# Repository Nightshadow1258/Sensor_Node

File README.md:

# Sensor Node Version 3.50
This is an intermediate version before I decided to move to a two part design.
I split the MCU Board into its own small form factor PCB with connectors on the bottom side to connect to a base board. The inspiration comes from the raspberry compute module. This will allow me to reuse the MCU for different design in the future.

## Components
- NRF52840 (MCU)
- NPM1300 (PMIC)
- BQ29700 (Battery Protection IC)
- SHT40 (Temp & Humidity Sensor)
- USB (charging & data transfer)

# Archive Notice

This repository has been archived and is no longer maintained.
It contains historical versions of the Sensor Node project (V1.00, V2.00, etc.)
for reference and backup purposes.

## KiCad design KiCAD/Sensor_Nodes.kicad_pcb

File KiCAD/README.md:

# Sensor Node V3.00 Hardware
This folder contains the KiCAD files for the Sensor Node Version 3.00.

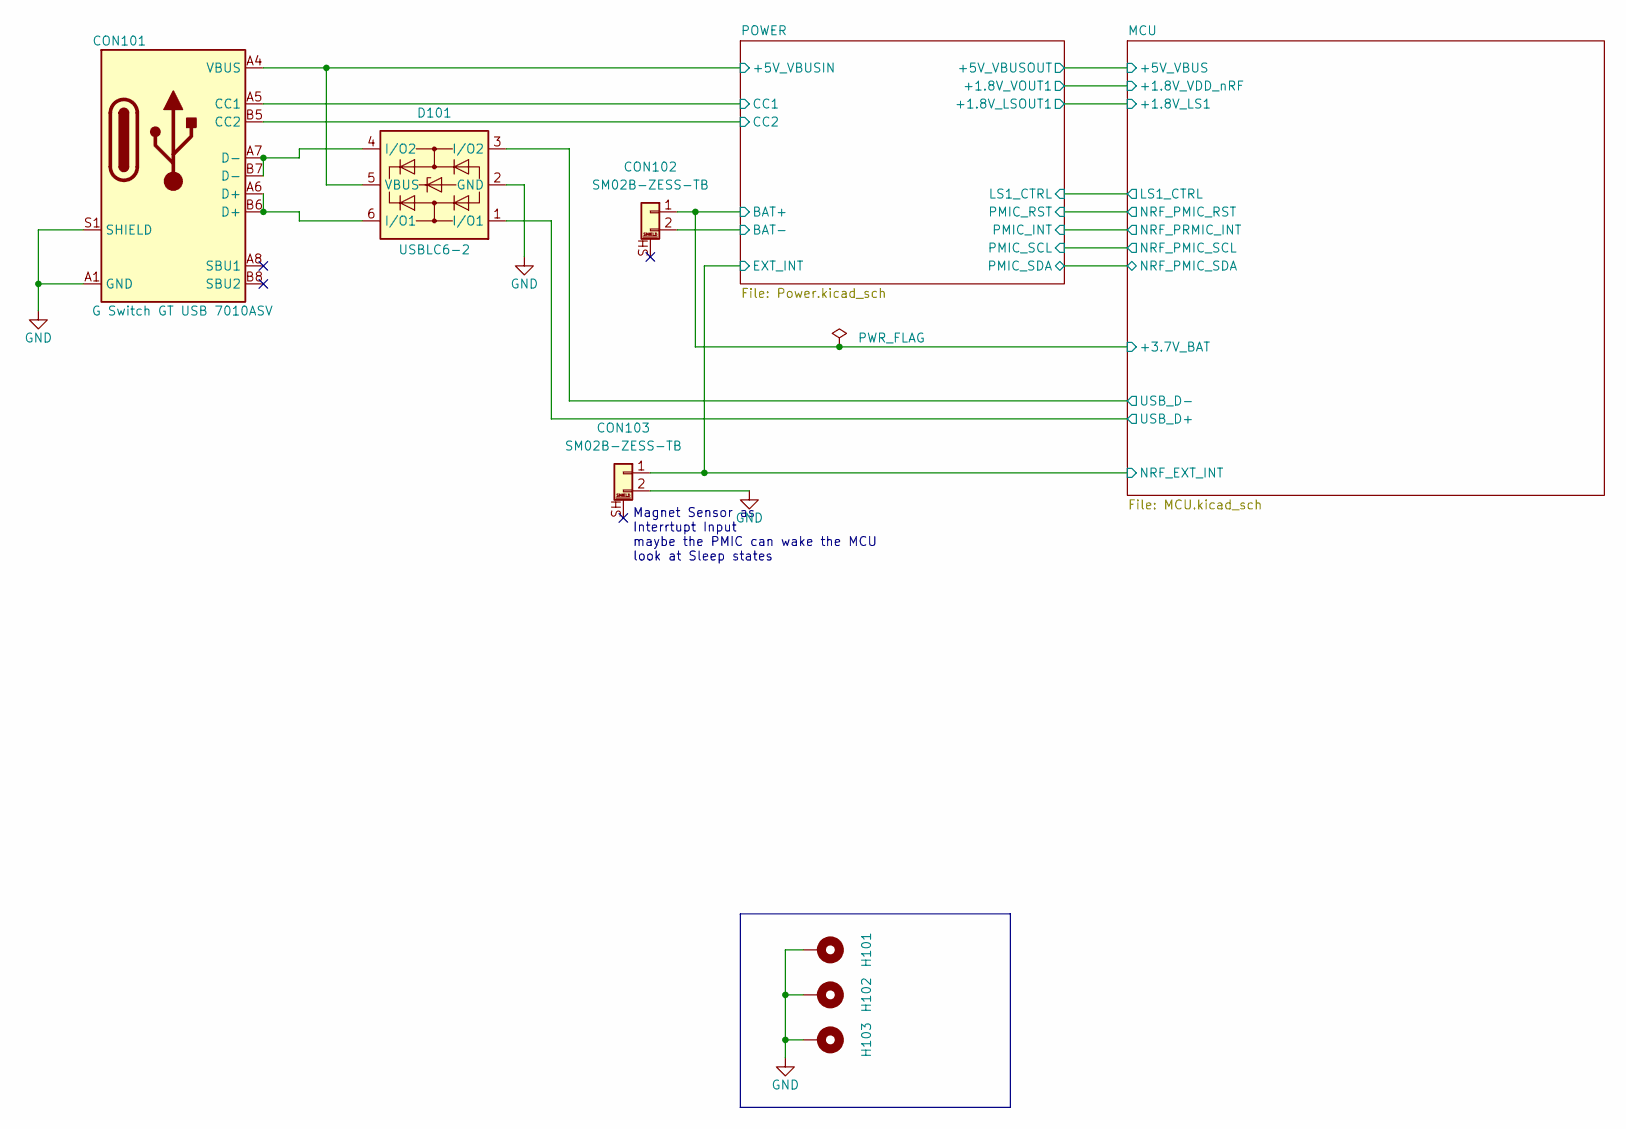
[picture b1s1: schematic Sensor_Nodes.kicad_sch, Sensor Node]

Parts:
CON101: G Switch GT USB 7010ASV; CON-GEN-USB_C-16P; LCSC Part # C2988369
CON102, CON103: SM02B-ZESS-TB; CON-SM02B-ZESS_TB
D101: USBLC6-2; SOT-23-6; LCSC Part # C7519
H101, H102, H103: MountingHole_Pad; MountingHole_3.2mm_M3_Pad_Via

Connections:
/MCU/NRF_EXT_INT: CON103.1; also elsewhere on the board
/MCU/USB_D+: D101.1 (I/O1); also elsewhere on the board
/MCU/USB_D-: D101.3 (I/O2); also elsewhere on the board
/POWER/+5V_VBUSIN: CON101.A4 (VBUS), CON101.A9 (VBUS), CON101.B4 (VBUS), CON101.B9 (VBUS), D101.5 (VBUS); also elsewhere on the board
/POWER/CC1: CON101.A5 (CC1); also elsewhere on the board
/POWER/CC2: CON101.B5 (CC2); also elsewhere on the board
GND: CON101.A1 (GND), CON101.A12 (GND), CON101.B1 (GND), CON101.B12 (GND), CON101.S1 (SHIELD), CON103.2, D101.2 (GND), H101.1, H102.1, H103.1; also elsewhere on the board
unnamed: CON101.A6 (D+), CON101.B6 (D+), D101.6 (I/O1)
unnamed: CON101.A7 (D-), CON101.B7 (D-), D101.4 (I/O2)

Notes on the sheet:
Magnet Sensor as Interrtupt Input maybe the PMIC can wake the MCU look at Sleep states

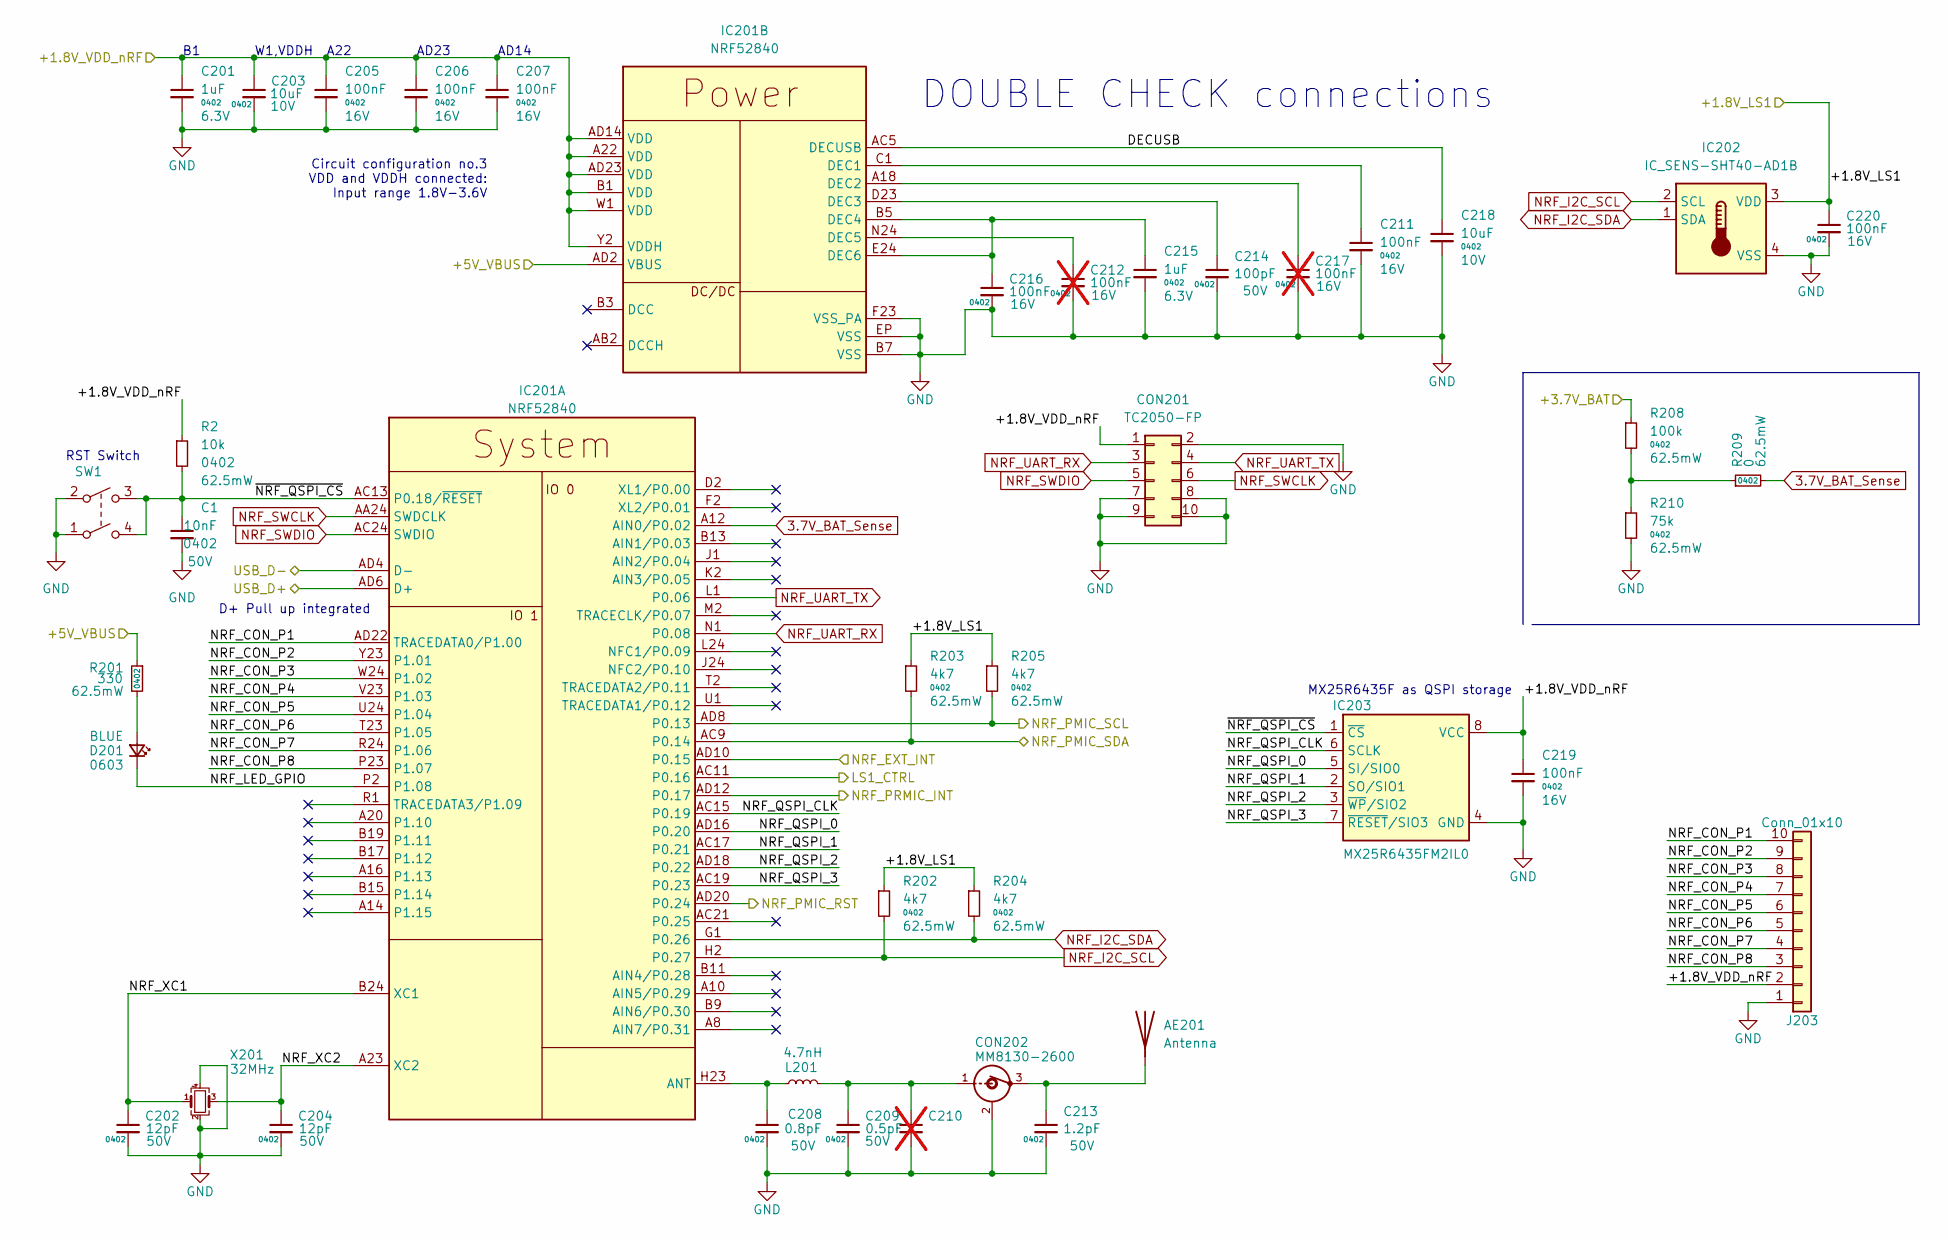
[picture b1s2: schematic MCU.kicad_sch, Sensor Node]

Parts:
AE201: Antenna; RF_ANT_NRF52840
C1: 10nF; C_0402_1005Metric; Voltage 50V; LCSC Part # C15195
C201, C215: 1uF; C_0402_1005Metric; Voltage 6.3V; LCSC Part # C15525
C202, C204: 12pF; C_0402_1005Metric; Voltage 50V; LCSC Part # C1547
C203, C218: 10uF; C_0603_1608Metric; Voltage 10V; LCSC Part # C96446
C205, C206, C207, C211, C216, C219, C220: 100nF; C_0402_1005Metric; Voltage 16V; LCSC Part # C1525
C208: 0.8pF; C_0402_1005Metric; Voltage 50V; LCSC Part # C327032
C209: 0.5pF; C_0402_1005Metric; Voltage 50V; LCSC Part # C285052
C210: C_0402_1005Metric; not fitted
C212, C217: 100nF; C_0402_1005Metric; Voltage 16V; LCSC Part # C1525; not fitted
C213: 1.2pF; C_0402_1005Metric; Voltage 50V; LCSC Part #q C1551
C214: 100pF; C_0402_1005Metric; Voltage 50V; LCSC Part # C1546
CON201: TC2050-FP; CON-TAG-CONNECT_TC2050-IDC
CON202: MM8130-2600; CON-BNC-MM8130-2600; LCSC Part # C167503
D201: BLUE; D_0603_1608Metric; LCSC Part # C965807
IC201: NRF52840; AQFN_73-EP_7x7mm_P0.5mm; LCSC Part # C190794
IC202: IC_SENS-SHT40-AD1B; DNF-1.5x1.5_H0.54-SHT40-AD1B; LCSC Part # C2848306
IC203: MX25R6435FM2IL0; SOP-8_5.28x5.23mm_P1.27mm; LCSC Part # C2802844
J203: Conn_01x10; PinHeader_1x10_P2.54mm_Vertical
L201: 4.7nH; L_0402_1005Metric; LCSC Part # C275292
R2: 10k; R_0402_1005Metric; Power Rating 62.5mW; LCSC Part # C25744
R201: 330; R_0402_1005Metric; Power Rating 62.5mW; LCSC Part # C25104
R202, R203, R204, R205: 4k7; R_0402_1005Metric; Power Rating 62.5mW; LCSC Part # C25900
R208: 100k; R_0402_1005Metric; Power Rating 62.5mW; LCSC Part # C25741
R209: 0; R_0402_1005Metric; Power Rating 62.5mW; LCSC Part # C17168
R210: 75k; R_0402_1005Metric; Power Rating 62.5mW; LCSC Part # C25798
SW1: SW-GEN-TS-1187A; SW-PUSH-DPST-XKS-TS-1187A; LCSC Part # C318884
X201: 32MHz; Crystal_SMD_3225-4Pin_3.2x2.5mm; LCSC Part # C2901708

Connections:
3.7V_BAT_Sense: IC201.A12 (AIN0/P0.02), R209.2
/MCU/+1.8V_LS1: C220.1, IC202.3 (VDD), R202.1, R203.1, R204.1, R205.1; also elsewhere on the board
/MCU/+1.8V_VDD_nRF: C201.1, C203.1, C205.1, C206.1, C207.1, C219.1, CON201.1, IC201.A22 (VDD), IC201.AD14 (VDD), IC201.AD23 (VDD), IC201.B1 (VDD), IC201.W1 (VDD), IC201.Y2 (VDDH), IC203.8 (VCC), J203.2, R2.1; also elsewhere on the board
/MCU/+3.7V_BAT: R208.1; also elsewhere on the board
/MCU/+5V_VBUS: IC201.AD2 (VBUS), R201.1; also elsewhere on the board
/MCU/DECUSB: C218.1, IC201.AC5 (DECUSB)
/MCU/LS1_CTRL: IC201.AC11 (P0.16); also elsewhere on the board
/MCU/NRF_CON_P1: IC201.AD22 (TRACEDATA0/P1.00), J203.10
/MCU/NRF_CON_P2: IC201.Y23 (P1.01), J203.9
/MCU/NRF_CON_P3: IC201.W24 (P1.02), J203.8
/MCU/NRF_CON_P4: IC201.V23 (P1.03), J203.7
/MCU/NRF_CON_P5: IC201.U24 (P1.04), J203.6
/MCU/NRF_CON_P6: IC201.T23 (P1.05), J203.5
/MCU/NRF_CON_P7: IC201.R24 (P1.06), J203.4
/MCU/NRF_CON_P8: IC201.P23 (P1.07), J203.3
/MCU/NRF_EXT_INT: IC201.AD10 (P0.15); also elsewhere on the board
/MCU/NRF_LED_GPIO: D201.1 (K), IC201.P2 (P1.08)
/MCU/NRF_PMIC_SCL: IC201.AD8 (P0.13), R205.2; also elsewhere on the board
/MCU/NRF_PMIC_SDA: IC201.AC9 (P0.14), R203.2; also elsewhere on the board
/MCU/NRF_PRMIC_INT: IC201.AD12 (P0.17); also elsewhere on the board
/MCU/NRF_QSPI_0: IC201.AD16 (P0.20), IC203.5 (SI/SIO0)
/MCU/NRF_QSPI_1: IC201.AC17 (P0.21), IC203.2 (SO/SIO1)
/MCU/NRF_QSPI_2: IC201.AD18 (P0.22), IC203.3 (~WP/SIO2)
/MCU/NRF_QSPI_3: IC201.AC19 (P0.23), IC203.7 (~RESET/SIO3)
/MCU/NRF_QSPI_CLK: IC201.AC15 (P0.19), IC203.6 (SCLK)
/MCU/NRF_XC1: C202.1, IC201.B24 (XC1), X201.1
/MCU/NRF_XC2: C204.1, IC201.A23 (XC2), X201.3
/MCU/USB_D+: IC201.AD6 (D+); also elsewhere on the board
/MCU/USB_D-: IC201.AD4 (D-); also elsewhere on the board
/MCU/~NRF_QSPI_CS: C1.1, IC201.AC13 (P0.18/~RESET), IC203.1 (~CS), R2.2, SW1.3 (4), SW1.4
/POWER/PMIC_RST: IC201.AD20 (P0.24); also elsewhere on the board
GND: C1.2, C201.2, C202.2, C203.2, C204.2, C205.2, C206.2, C207.2, C208.2, C209.2, C210.2, C211.2, C212.2, C213.2, C214.2, C215.2, C216.2, C217.2, C218.2, C219.2, C220.2, CON201.2, CON201.7, CON201.8, CON201.9, CON201.10, CON202.2, IC201.B7 (VSS), IC201.EP (VSS), IC201.F23 (VSS_PA), IC202.4 (VSS), IC203.4 (GND), J203.1, R210.2, SW1.1, SW1.2 (3), X201.2, X201.4; also elsewhere on the board
NRF_I2C_SCL: IC201.H2 (P0.27), IC202.2 (SCL), R202.2
NRF_I2C_SDA: IC201.G1 (P0.26), IC202.1 (SDA), R204.2
NRF_SWCLK: CON201.6, IC201.AA24 (SWDCLK)
NRF_SWDIO: CON201.5, IC201.AC24 (SWDIO)
NRF_UART_RX: CON201.3, IC201.N1 (P0.08)
NRF_UART_TX: CON201.4, IC201.L1 (P0.06)
unnamed: AE201.1 (A), C213.1, CON202.3
unnamed: C209.1, C210.1, CON202.1, L201.1
unnamed: D201.2 (A), R201.2
unnamed: C208.1, IC201.H23 (ANT), L201.2
unnamed: C211.1, IC201.C1 (DEC1)
unnamed: C217.1, IC201.A18 (DEC2)
unnamed: C214.1, IC201.D23 (DEC3)
unnamed: C215.1, C216.1, IC201.B5 (DEC4), IC201.E24 (DEC6)
unnamed: C212.1, IC201.N24 (DEC5)
unnamed: R208.2, R209.1, R210.1

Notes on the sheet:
RST Switch
AD23
Circuit configuration no.3 VDD and VDDH connected: Input range 1.8V-3.6V
DOUBLE CHECK connections
A22
AD14
W1,VDDH
MX25R6435F as QSPI storage
D+ Pull up integrated

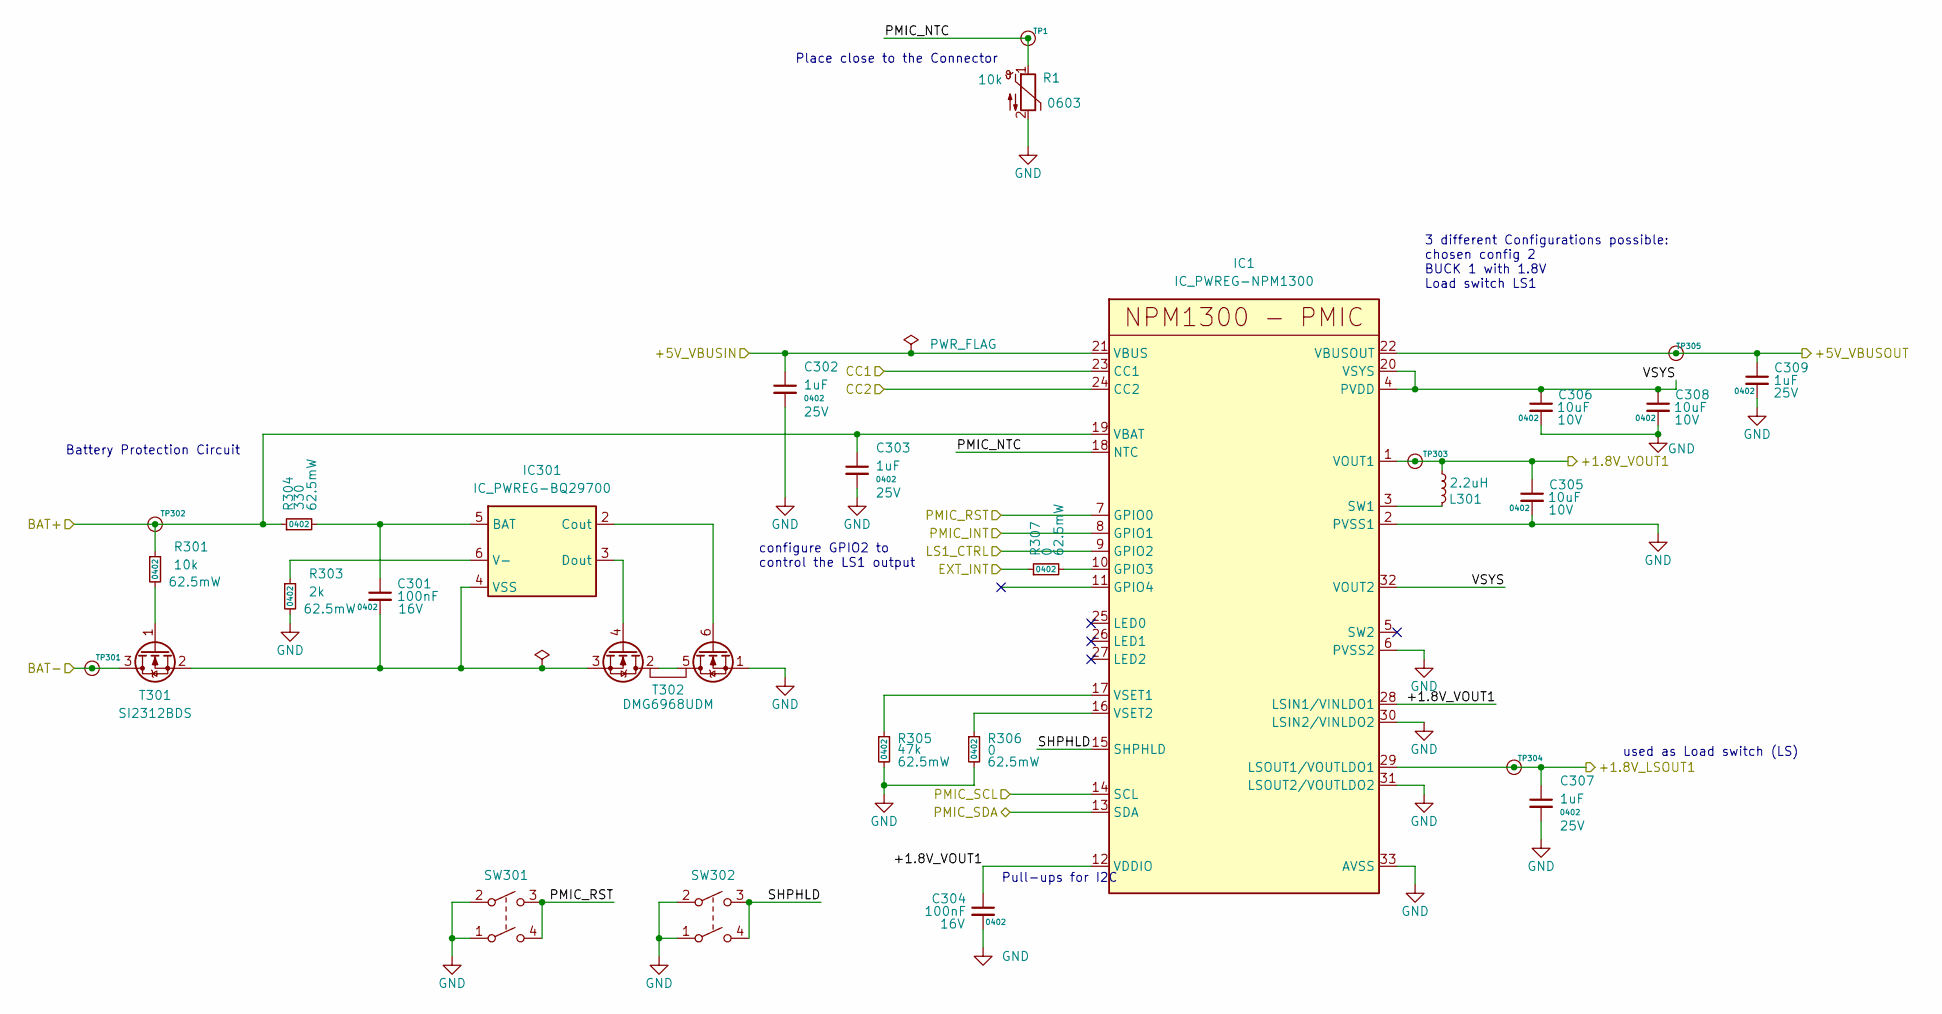
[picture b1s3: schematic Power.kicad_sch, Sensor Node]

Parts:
C301, C304: 100nF; C_0402_1005Metric; Voltage 16V; LCSC Part # C1525
C302, C303, C307, C309: 1uF; C_0402_1005Metric; Voltage 25V; LCSC Part # C52923
C305, C306, C308: 10uF; C_0603_1608Metric; Voltage 10V; LCSC Part # C96446
IC1: IC_PWREG-NPM1300; QFN-32-1EP_5x5mm_P0.5mm_EP3.6x3.6mm_ThermalVias
IC301: IC_PWREG-BQ29700; WSON-6_1.5x1.5mm_P0.5mm; LCSC Part # C183096
L301: 2.2uH; L_0806; LCSC Part # C2838367
R1: 10k; R_0603_1608Metric; LCSC Part # C142556
R301: 10k; R_0402_1005Metric; Power Rating 62.5mW; LCSC Part # C25744
R303: 2k; R_0402_1005Metric; Power Rating 62.5mW; LCSC Part # C4109
R304: 330; R_0402_1005Metric; Power Rating 62.5mW; LCSC Part # C25104
R305: 47k; R_0402_1005Metric; Power Rating 62.5mW; LCSC Part # C25792
R306, R307: 0; R_0402_1005Metric; Power Rating 62.5mW; LCSC Part # C17168
SW301, SW302: SW-GEN-TS-1187A; SW-PUSH-DPST-XKS-TS-1187A; LCSC Part # C318884
T301: SI2312BDS; SOT-23; LCSC Part # C351405
T302: DMG6968UDM; SOT-23-6; LCSC Part # C2762931
TP1, TP301, TP302, TP303, TP304, TP305: TP; TP_Pad_D0.9mm

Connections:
/MCU/+1.8V_LS1: C307.1, IC1.29 (LSOUT1/VOUTLDO1), TP304.1; also elsewhere on the board
/MCU/+1.8V_VDD_nRF: C304.1, C305.1, IC1.1 (VOUT1), IC1.12 (VDDIO), IC1.28 (LSIN1/VINLDO1), L301.1, TP303.1; also elsewhere on the board
/MCU/+3.7V_BAT: C303.1, IC1.19 (VBAT), R301.1, R304.1, TP302.1; also elsewhere on the board
/MCU/+5V_VBUS: C309.1, IC1.22 (VBUSOUT), TP305.1; also elsewhere on the board
/MCU/LS1_CTRL: IC1.9 (GPIO2); also elsewhere on the board
/MCU/NRF_EXT_INT: R307.1; also elsewhere on the board
/MCU/NRF_PMIC_SCL: IC1.14 (SCL); also elsewhere on the board
/MCU/NRF_PMIC_SDA: IC1.13 (SDA); also elsewhere on the board
/MCU/NRF_PRMIC_INT: IC1.8 (GPIO1); also elsewhere on the board
/POWER/+5V_VBUSIN: C302.1, IC1.21 (VBUS); also elsewhere on the board
/POWER/BAT-: T301.3 (D), TP301.1; also elsewhere on the board
/POWER/CC1: IC1.23 (CC1); also elsewhere on the board
/POWER/CC2: IC1.24 (CC2); also elsewhere on the board
/POWER/PMIC_NTC: IC1.18 (NTC), R1.1, TP1.1
/POWER/PMIC_RST: IC1.7 (GPIO0), SW301.3 (4), SW301.4; also elsewhere on the board
/POWER/SHPHLD: IC1.15 (SHPHLD), SW302.3 (4), SW302.4
/POWER/VSYS: C306.1, C308.1, IC1.4 (PVDD), IC1.20 (VSYS), IC1.32 (VOUT2)
GND: C302.2, C303.2, C304.2, C305.2, C306.2, C307.2, C308.2, C309.2, IC1.2 (PVSS1), IC1.6 (PVSS2), IC1.30 (LSIN2/VINLDO2), IC1.31 (LSOUT2/VOUTLDO2), IC1.33 (AVSS), R1.2, R303.2, R305.2, R306.2, SW301.1, SW301.2 (3), SW302.1, SW302.2 (3), T302.1 (S1); also elsewhere on the board
unnamed: IC1.10 (GPIO3), R307.2
unnamed: IC1.3 (SW1), L301.2
unnamed: IC1.17 (VSET1), R305.1
unnamed: IC1.16 (VSET2), R306.1
unnamed: C301.1, IC301.5 (BAT), R304.2
unnamed: IC301.2 (Cout), T302.6 (G1)
unnamed: IC301.3 (Dout), T302.4 (G2)
unnamed: IC301.6 (V-), R303.1
unnamed 64: C301.2, IC301.4 (VSS), T301.2 (S), T302.3 (S2); also elsewhere on the board
unnamed: R301.2, T301.1 (G)
unnamed: T302.2 (D1/D2), T302.5 (D1/D2)

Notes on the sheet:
Pull-ups for I2C
Battery Protection Circuit
Place close to the Connector
3 different Configurations possible: chosen config 2 BUCK 1 with 1.8V Load switch LS1
configure GPIO2 to control the LS1 output
used as Load switch (LS)

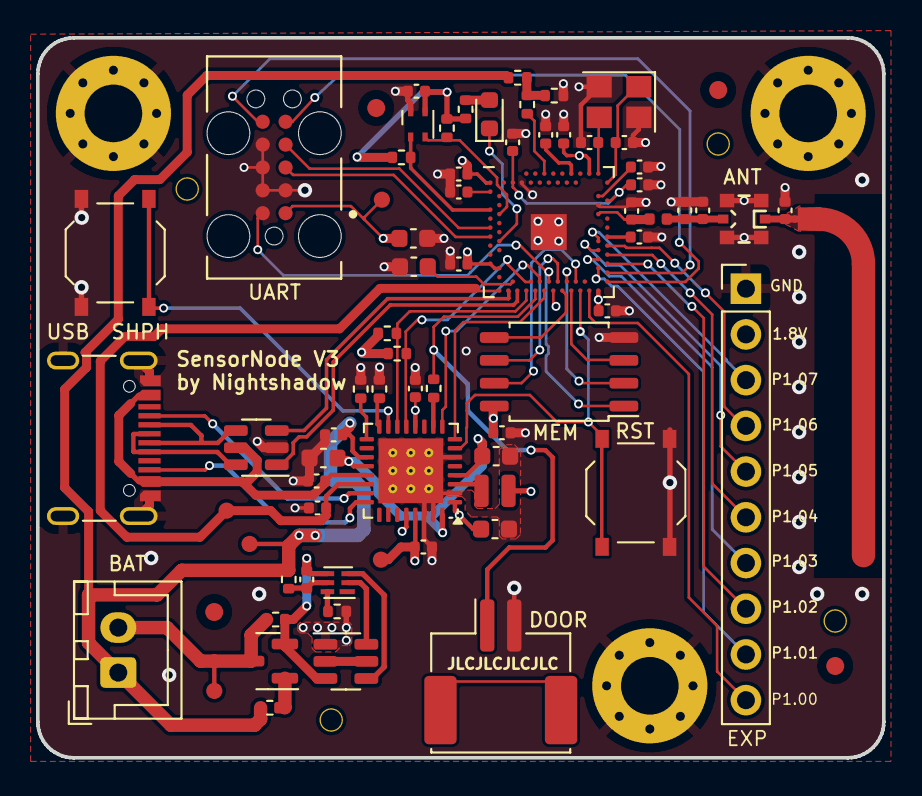
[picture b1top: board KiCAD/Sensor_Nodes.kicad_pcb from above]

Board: 4 copper layers, 47.0 x 40.0 mm, 81 parts (0 on the bottom side), 67 nets.

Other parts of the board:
C102: Conn_01x02; JST_XH_B2B-XH-A_1x02_P2.50mm_Vertical
FID101, FID102, FID103, FID104: Fiducial; Fiducial_1mm_Mask2mm
PCB101, PCB102, PCB103, PCB104: Tooling Hole JLCPCB; PCB-TH-NP-JLCPCB
R302: 330; R_0402_1005Metric

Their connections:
/MCU/+3.7V_BAT: C102.1; also elsewhere on the board
/POWER/BAT-: C102.2, R302.2; also elsewhere on the board
unnamed 64: R302.1; also elsewhere on the board

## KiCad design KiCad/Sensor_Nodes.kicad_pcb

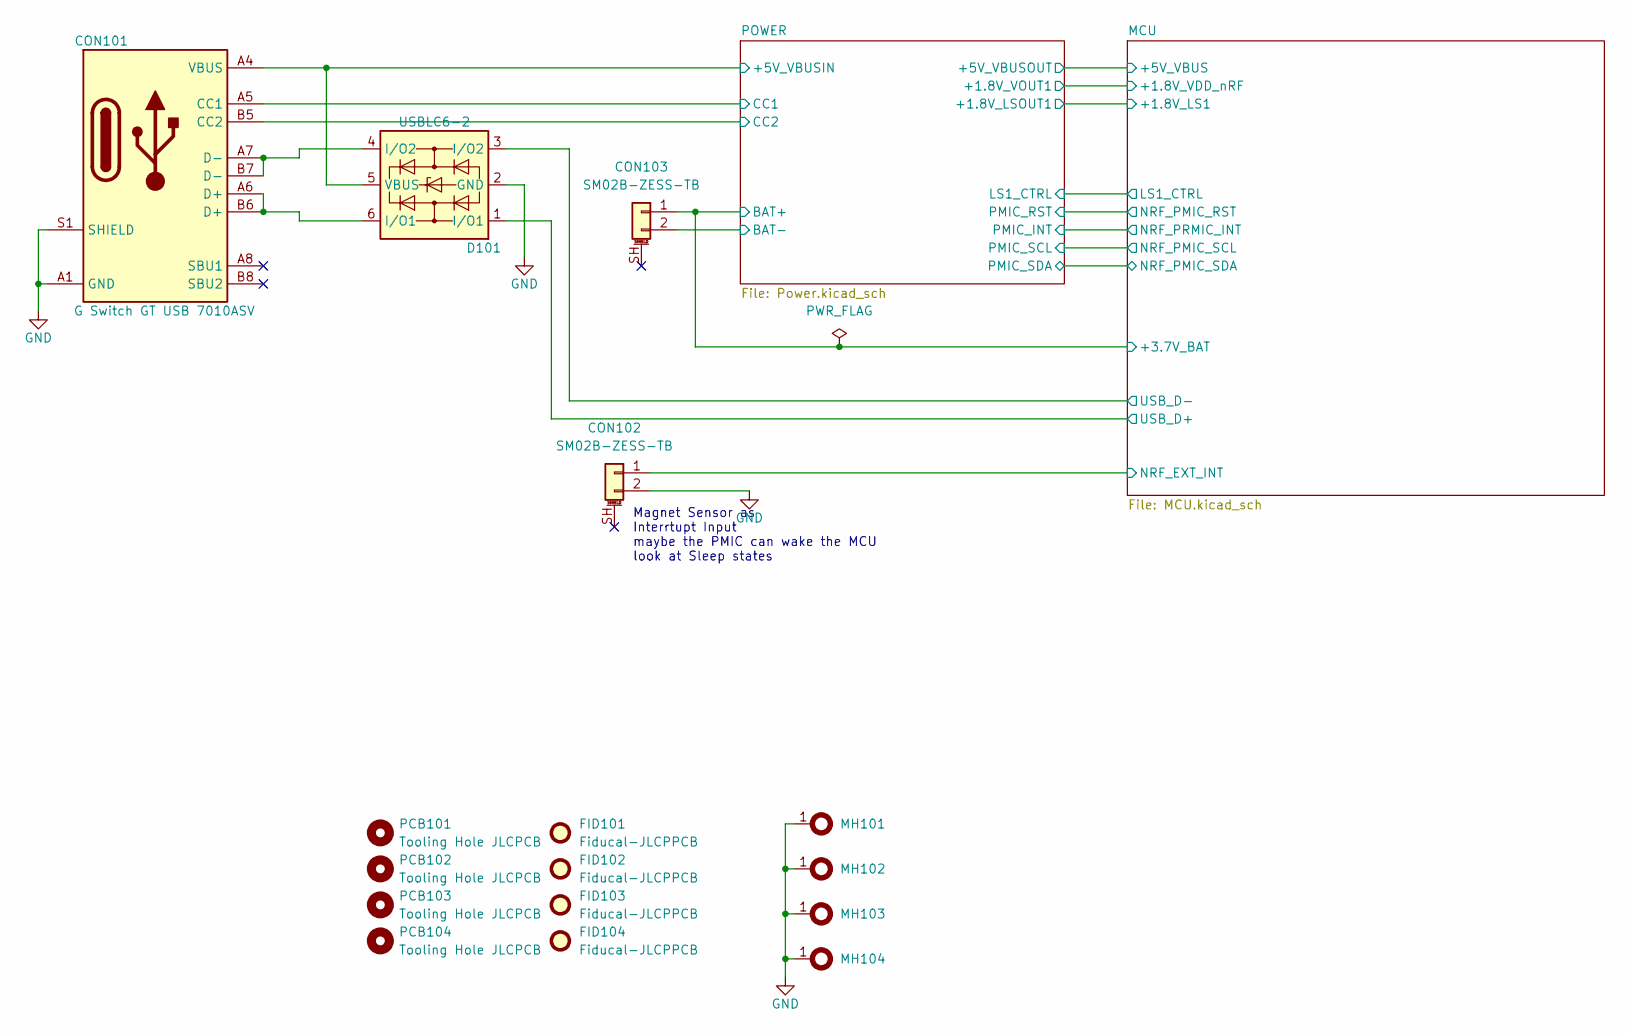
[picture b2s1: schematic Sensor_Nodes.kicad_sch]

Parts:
CON101: G Switch GT USB 7010ASV; CON-GEN-USB_C-16P; LCSC Part # C2988369
CON102, CON103: SM02B-ZESS-TB; CON-SM02B-ZESS_TB
D101: USBLC6-2; SOT-23-6; LCSC Part # C7519
FID101, FID102, FID103, FID104: Fiducal-JLCPPCB; Fiducal-JLCPCB
MH101, MH102, MH103, MH104: MountingHole_2.5mm_Pad_Via
PCB101, PCB102, PCB103, PCB104: Tooling Hole JLCPCB; PCB-NPTH-JLCPCB

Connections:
/MCU/+3.7V_BAT: CON103.1; also elsewhere on the board
/MCU/NRF_EXT_INT: CON102.1; also elsewhere on the board
/MCU/USB_D+: D101.1 (I/O1); also elsewhere on the board
/MCU/USB_D-: D101.3 (I/O2); also elsewhere on the board
/POWER/+5V_VBUSIN: CON101.A4 (VBUS), CON101.A9 (VBUS), CON101.B4 (VBUS), CON101.B9 (VBUS), D101.5 (VBUS); also elsewhere on the board
/POWER/BAT-: CON103.2; also elsewhere on the board
/POWER/CC1: CON101.A5 (CC1); also elsewhere on the board
/POWER/CC2: CON101.B5 (CC2); also elsewhere on the board
GND: CON101.A1 (GND), CON101.A12 (GND), CON101.B1 (GND), CON101.B12 (GND), CON101.S1 (SHIELD), CON102.2, D101.2 (GND), MH101.1, MH102.1, MH103.1, MH104.1; also elsewhere on the board
unnamed: CON101.A6 (D+), CON101.B6 (D+), D101.6 (I/O1)
unnamed: CON101.A7 (D-), CON101.B7 (D-), D101.4 (I/O2)

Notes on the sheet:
Magnet Sensor as Interrtupt Input maybe the PMIC can wake the MCU look at Sleep states

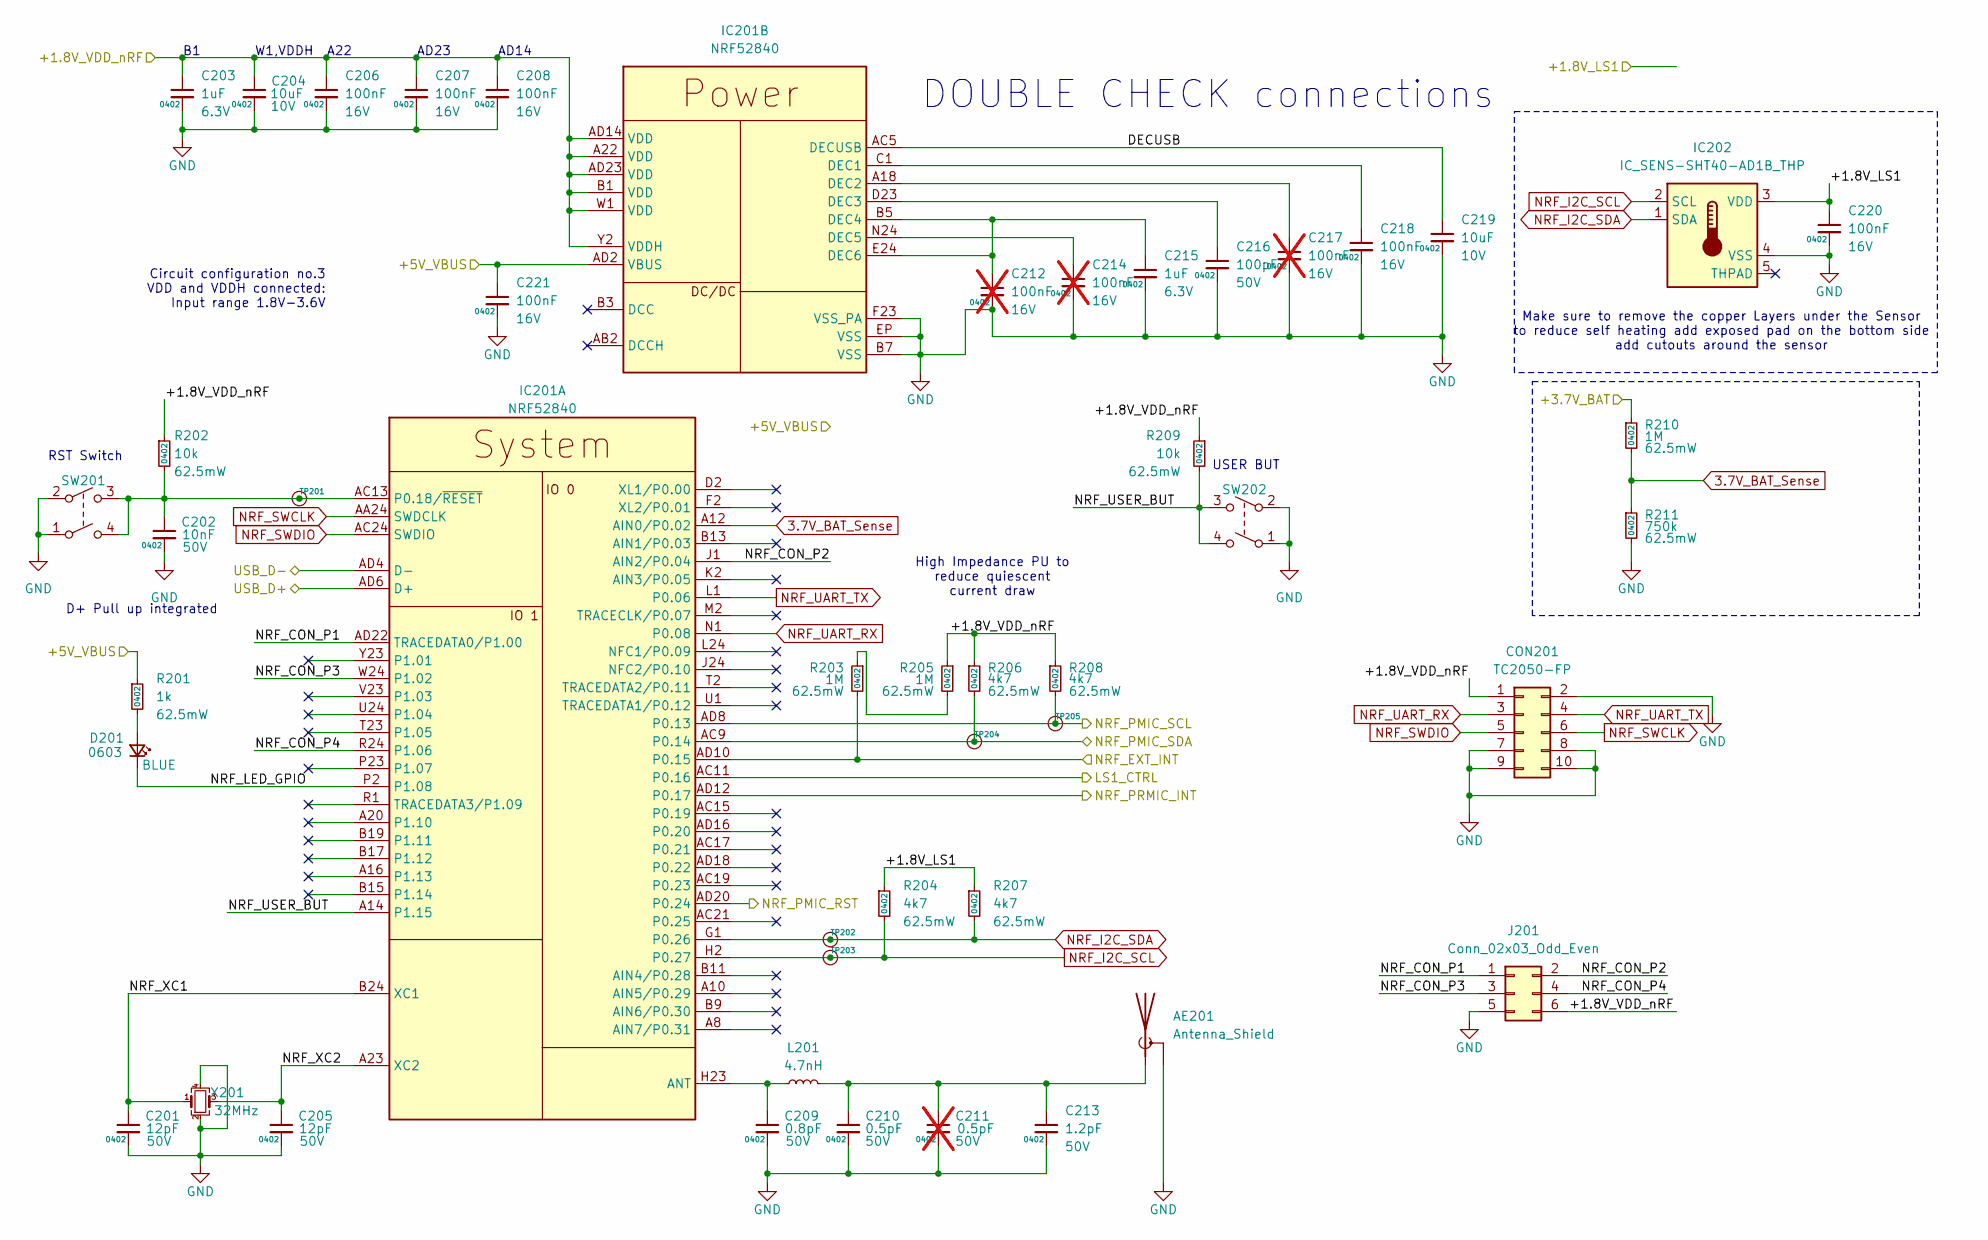
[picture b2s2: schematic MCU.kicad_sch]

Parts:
AE201: Antenna_Shield; Texas_SWRA117D_2.4GHz_Right
C201, C205: 12pF; C_0402_1005Metric; Voltage 50V; LCSC Part # C1547
C202: 10nF; C_0402_1005Metric; Voltage 50V; LCSC Part # C15195
C203, C215: 1uF; C_0402_1005Metric; Voltage 6.3V; LCSC Part # C15525
C204, C219: 10uF; C_0603_1608Metric; Voltage 10V; LCSC Part # C96446
C206, C207, C208, C218, C220, C221: 100nF; C_0402_1005Metric; Voltage 16V; LCSC Part # C1525
C209: 0.8pF; C_0402_1005Metric; Voltage 50V; LCSC Part # C327032
C210: 0.5pF; C_0402_1005Metric; Voltage 50V; LCSC Part # C285052
C211: 0.5pF; C_0402_1005Metric; Voltage 50V; LCSC Part # C285052; not fitted
C212, C214, C217: 100nF; C_0402_1005Metric; Voltage 16V; LCSC Part # C1525; not fitted
C213: 1.2pF; C_0402_1005Metric; Voltage 50V; LCSC Part #q C1551
C216: 100pF; C_0402_1005Metric; Voltage 50V; LCSC Part # C1546
CON201: TC2050-FP; CON-TAG-CONNECT_TC2050-IDC
D201: BLUE; D_0603_1608Metric; LCSC Part # C72041
IC201: NRF52840; Nordic_AQFN-73-1EP_7x7mm_P0.5mm; LCSC Part # C190794
IC202: IC_SENS-SHT40-AD1B_THP; DNF-1.5x1.5_H0.54-SHT40-AD1B_THPAD
J201: Conn_02x03_Odd_Even; PinHeader_2x03_P2.54mm_Vertical
L201: 4.7nH; L_0402_1005Metric; LCSC Part # C370227
R201: 1k; R_0402_1005Metric; Power Rating 62.5mW; LCSC Part # C11702
R202, R209: 10k; R_0402_1005Metric; Power Rating 62.5mW; LCSC Part # C25744
R203, R205, R210: 1M; R_0402_1005Metric; Power Rating 62.5mW; LCSC Part # C138033
R204, R206, R207, R208: 4k7; R_0402_1005Metric; Power Rating 62.5mW; LCSC Part # C25900
R211: 750k; R_0402_1005Metric; Power Rating 62.5mW; LCSC Part # C137937
SW201, SW202: SW-GEN-TS-1187A; SW-PUSH-DPST-XKS-TS-1187A; LCSC Part # C318884
TP201, TP202, TP203, TP204, TP205: TP; TP_Pad_D0.9mm
X201: 32MHz; Crystal_SMD_3225-4Pin_3.2x2.5mm; LCSC Part # C2901708

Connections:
3.7V_BAT_Sense: IC201.A12 (AIN0/P0.02), R210.2, R211.1
/MCU/+1.8V_LS1: C220.1, IC202.3 (VDD), R204.1, R207.1; also elsewhere on the board
/MCU/+1.8V_VDD_nRF: C203.1, C204.1, C206.1, C207.1, C208.1, CON201.1, IC201.A22 (VDD), IC201.AD14 (VDD), IC201.AD23 (VDD), IC201.B1 (VDD), IC201.W1 (VDD), IC201.Y2 (VDDH), J201.6, R202.1, R205.1, R206.1, R208.1, R209.1; also elsewhere on the board
/MCU/+3.7V_BAT: R210.1; also elsewhere on the board
/MCU/+5V_VBUS: C221.1, IC201.AD2 (VBUS), R201.1; also elsewhere on the board
/MCU/DECUSB: C219.1, IC201.AC5 (DECUSB)
/MCU/LS1_CTRL: IC201.AC11 (P0.16); also elsewhere on the board
/MCU/NRF_CON_P1: IC201.AD22 (TRACEDATA0/P1.00), J201.1
/MCU/NRF_CON_P2: IC201.J1 (AIN2/P0.04), J201.2
/MCU/NRF_CON_P3: IC201.W24 (P1.02), J201.3
/MCU/NRF_CON_P4: IC201.R24 (P1.06), J201.4
/MCU/NRF_EXT_INT: IC201.AD10 (P0.15), R203.2; also elsewhere on the board
/MCU/NRF_LED_GPIO: D201.1 (K), IC201.P2 (P1.08)
/MCU/NRF_PMIC_RST: IC201.AD20 (P0.24); also elsewhere on the board
/MCU/NRF_PMIC_SCL: IC201.AD8 (P0.13), R208.2, TP205.1; also elsewhere on the board
/MCU/NRF_PMIC_SDA: IC201.AC9 (P0.14), R206.2, TP204.1; also elsewhere on the board
/MCU/NRF_PRMIC_INT: IC201.AD12 (P0.17); also elsewhere on the board
/MCU/NRF_USER_BUT: IC201.A14 (P1.15), R209.2, SW202.3 (4), SW202.4
/MCU/NRF_XC1: C201.1, IC201.B24 (XC1), X201.1
/MCU/NRF_XC2: C205.1, IC201.A23 (XC2), X201.3
/MCU/USB_D+: IC201.AD6 (D+); also elsewhere on the board
/MCU/USB_D-: IC201.AD4 (D-); also elsewhere on the board
GND: AE201.2 (Shield), C201.2, C202.2, C203.2, C204.2, C205.2, C206.2, C207.2, C208.2, C209.2, C210.2, C211.2, C212.2, C213.2, C214.2, C215.2, C216.2, C217.2, C218.2, C219.2, C220.2, C221.2, CON201.2, CON201.7, CON201.8, CON201.9, CON201.10, IC201.B7 (VSS), IC201.EP (VSS), IC201.F23 (VSS_PA), IC202.4 (VSS), J201.5, R211.2, SW201.1, SW201.2 (3), SW202.1, SW202.2 (3), X201.2, X201.4; also elsewhere on the board
NRF_I2C_SCL: IC201.H2 (P0.27), IC202.2 (SCL), R204.2, TP203.1
NRF_I2C_SDA: IC201.G1 (P0.26), IC202.1 (SDA), R207.2, TP202.1
NRF_SWCLK: CON201.6, IC201.AA24 (SWDCLK)
NRF_SWDIO: CON201.5, IC201.AC24 (SWDIO)
NRF_UART_RX: CON201.3, IC201.N1 (P0.08)
NRF_UART_TX: CON201.4, IC201.L1 (P0.06)
unnamed: AE201.1 (A), C210.1, C211.1, C213.1, L201.2
unnamed: D201.2 (A), R201.2
unnamed: C209.1, IC201.H23 (ANT), L201.1
unnamed: C202.1, IC201.AC13 (P0.18/~RESET), R202.2, SW201.3 (4), SW201.4, TP201.1
unnamed: C218.1, IC201.C1 (DEC1)
unnamed: C217.1, IC201.A18 (DEC2)
unnamed: C216.1, IC201.D23 (DEC3)
unnamed: C212.1, C215.1, IC201.B5 (DEC4), IC201.E24 (DEC6)
unnamed: C214.1, IC201.N24 (DEC5)
unnamed: R203.1, R205.2

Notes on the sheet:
AD23
Circuit configuration no.3 VDD and VDDH connected: Input range 1.8V-3.6V
DOUBLE CHECK connections
USER BUT
A22
High Impedance PU to reduce quiescent current draw
AD14
Make sure to remove the copper Layers under the Sensor to reduce self heating add exposed pad on the bottom side add cutouts around the sensor
W1,VDDH
RST Switch
D+ Pull up integrated
